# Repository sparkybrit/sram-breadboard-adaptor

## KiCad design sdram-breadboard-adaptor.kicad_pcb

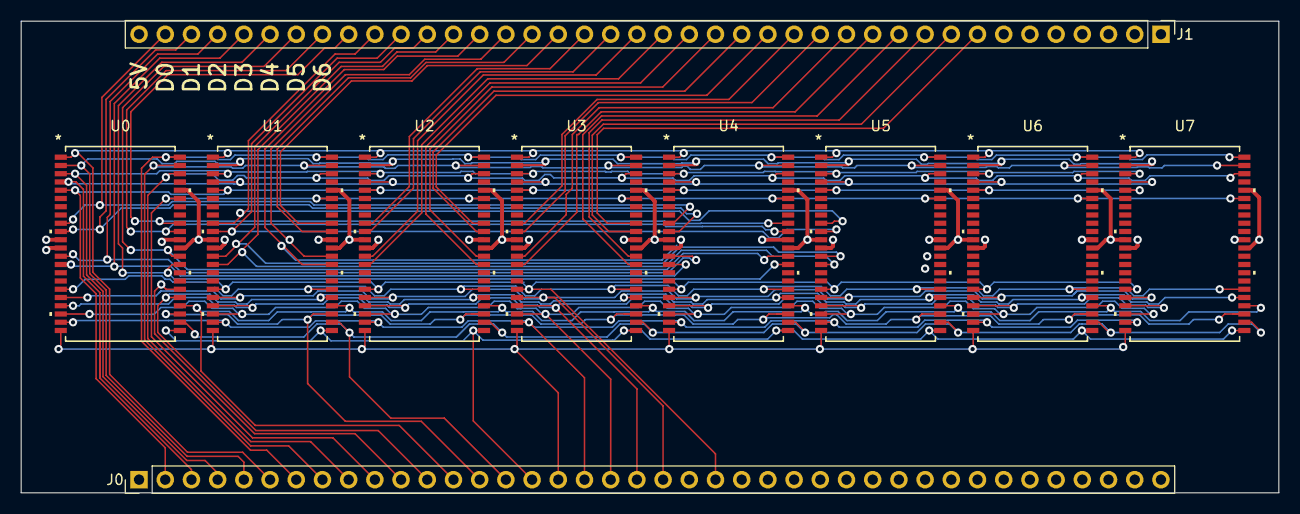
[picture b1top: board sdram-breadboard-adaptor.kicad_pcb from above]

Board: 4 copper layers, 121.9 x 45.7 mm, 10 parts (0 on the bottom side), 63 nets.

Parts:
J0, J1: Conn_01x40; PinHeader_1x40_P2.54mm_Vertical
U0, U1, U2, U3, U4, U5, U6, U7: LY62W10248ML-55LLI; TSOP-II-44_400MIL_LTK

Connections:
+5V: J0.1, J1.40, U0.11 (VCC), U0.33 (VCC), U0.40 (CE2), U1.11 (VCC), U1.33 (VCC), U1.40 (CE2), U2.11 (VCC), U2.33 (VCC), U2.40 (CE2), U3.11 (VCC), U3.33 (VCC), U3.40 (CE2), U4.11 (VCC), U4.33 (VCC), U4.40 (CE2), U5.11 (VCC), U5.33 (VCC), U5.40 (CE2), U6.11 (VCC), U6.33 (VCC), U6.40 (CE2), U7.11 (VCC), U7.33 (VCC), U7.40 (CE2)
/A2: J0.2, U0.5 (A0), U1.5 (A0), U2.5 (A0), U3.5 (A0), U4.5 (A0), U5.5 (A0), U6.5 (A0), U7.5 (A0)
/A3: J0.3, U0.4 (A1), U1.4 (A1), U2.4 (A1), U3.4 (A1), U4.4 (A1), U5.4 (A1), U6.4 (A1), U7.4 (A1)
/A4: J0.4, U0.3 (A2), U1.3 (A2), U2.3 (A2), U3.3 (A2), U4.3 (A2), U5.3 (A2), U6.3 (A2), U7.3 (A2)
/A5: J0.5, U0.2 (A3), U1.2 (A3), U2.2 (A3), U3.2 (A3), U4.2 (A3), U5.2 (A3), U6.2 (A3), U7.2 (A3)
/A6: J0.6, U0.1 (A4), U1.1 (A4), U2.1 (A4), U3.1 (A4), U4.1 (A4), U5.1 (A4), U6.1 (A4), U7.1 (A4)
/A7: J0.7, U0.44 (A5), U1.44 (A5), U2.44 (A5), U3.44 (A5), U4.44 (A5), U5.44 (A5), U6.44 (A5), U7.44 (A5)
/A8: J0.8, U0.43 (A6), U1.43 (A6), U2.43 (A6), U3.43 (A6), U4.43 (A6), U5.43 (A6), U6.43 (A6), U7.43 (A6)
/A9: J0.9, U0.42 (A7), U1.42 (A7), U2.42 (A7), U3.42 (A7), U4.42 (A7), U5.42 (A7), U6.42 (A7), U7.42 (A7)
/A10: J0.10, U0.39 (A8), U1.39 (A8), U2.39 (A8), U3.39 (A8), U4.39 (A8), U5.39 (A8), U6.39 (A8), U7.39 (A8)
/A11: J0.11, U0.28 (A9), U1.28 (A9), U2.28 (A9), U3.28 (A9), U4.28 (A9), U5.28 (A9), U6.28 (A9), U7.28 (A9)
/A12: J0.12, U0.27 (A10), U1.27 (A10), U2.27 (A10), U3.27 (A10), U4.27 (A10), U5.27 (A10), U6.27 (A10), U7.27 (A10)
/A13: J0.13, U0.26 (A11), U1.26 (A11), U2.26 (A11), U3.26 (A11), U4.26 (A11), U5.26 (A11), U6.26 (A11), U7.26 (A11)
/A14: J0.14, U0.25 (A12), U1.25 (A12), U2.25 (A12), U3.25 (A12), U4.25 (A12), U5.25 (A12), U6.25 (A12), U7.25 (A12)
/A15: J0.15, U0.24 (A13), U1.24 (A13), U2.24 (A13), U3.24 (A13), U4.24 (A13), U5.24 (A13), U6.24 (A13), U7.24 (A13)
/A16: J0.16, U0.23 (A14), U1.23 (A14), U2.23 (A14), U3.23 (A14), U4.23 (A14), U5.23 (A14), U6.23 (A14), U7.23 (A14)
/A17: J0.17, U0.22 (A15), U1.22 (A15), U2.22 (A15), U3.22 (A15), U4.22 (A15), U5.22 (A15), U6.22 (A15), U7.22 (A15)
/A18: J0.18, U0.21 (A16), U1.21 (A16), U2.21 (A16), U3.21 (A16), U4.21 (A16), U5.21 (A16), U6.21 (A16), U7.21 (A16)
/A19: J0.19, U0.20 (A17), U1.20 (A17), U2.20 (A17), U3.20 (A17), U4.20 (A17), U5.20 (A17), U6.20 (A17), U7.20 (A17)
/A20: J0.20, U0.19 (A18), U1.19 (A18), U2.19 (A18), U3.19 (A18), U4.19 (A18), U5.19 (A18), U6.19 (A18), U7.19 (A18)
/A21: J0.21, U0.18 (A19), U1.18 (A19), U2.18 (A19), U3.18 (A19), U4.18 (A19), U5.18 (A19), U6.18 (A19), U7.18 (A19)
/D0: J1.39, U0.9 (DQ0), U4.9 (DQ0)
/D1: J1.38, U0.10 (DQ1), U4.10 (DQ1)
/D2: J1.37, U0.13 (DQ2), U4.13 (DQ2)
/D3: J1.36, U0.14 (DQ3), U4.14 (DQ3)
/D4: J1.35, U0.31 (DQ4), U4.31 (DQ4)
/D5: J1.34, U0.32 (DQ5), U4.32 (DQ5)
/D6: J1.33, U0.35 (DQ6), U4.35 (DQ6)
/D7: J1.32, U0.36 (DQ7), U4.36 (DQ7)
/D8: J1.31, U1.9 (DQ0), U5.9 (DQ0)
/D9: J1.30, U1.10 (DQ1), U5.10 (DQ1)
/D10: J1.29, U1.13 (DQ2), U5.13 (DQ2)
/D11: J1.28, U1.14 (DQ3), U5.14 (DQ3)
/D12: J1.27, U1.31 (DQ4), U5.31 (DQ4)
/D13: J1.26, U1.32 (DQ5), U5.32 (DQ5)
/D14: J1.25, U1.35 (DQ6), U5.35 (DQ6)
/D15: J1.24, U1.36 (DQ7), U5.36 (DQ7)
/D16: J1.23, U2.9 (DQ0), U6.9 (DQ0)
/D17: J1.22, U2.10 (DQ1), U6.10 (DQ1)
/D18: J1.21, U2.13 (DQ2), U6.13 (DQ2)
/D19: J1.20, U2.14 (DQ3), U6.14 (DQ3)
/D20: J1.19, U2.31 (DQ4), U6.31 (DQ4)
/D21: J1.18, U2.32 (DQ5), U6.32 (DQ5)
/D22: J1.17, U2.35 (DQ6), U6.35 (DQ6)
/D23: J1.16, U2.36 (DQ7), U6.36 (DQ7)
/D24: J1.15, U3.9 (DQ0), U7.9 (DQ0)
/D25: J1.14, U3.10 (DQ1), U7.10 (DQ1)
/D26: J1.13, U3.13 (DQ2), U7.13 (DQ2)
/D27: J1.12, U3.14 (DQ3), U7.14 (DQ3)
/D28: J1.11, U3.31 (DQ4), U7.31 (DQ4)
/D29: J1.10, U3.32 (DQ5), U7.32 (DQ5)
/D30: J1.9, U3.35 (DQ6), U7.35 (DQ6)
/D31: J1.8, U3.36 (DQ7), U7.36 (DQ7)
/R/W: J0.23, U0.17 (WE#), U1.17 (WE#), U2.17 (WE#), U3.17 (WE#), U4.17 (WE#), U5.17 (WE#), U6.17 (WE#), U7.17 (WE#)
/~CEA0: J0.24, U0.6 (CE#)
/~CEA1: J0.25, U1.6 (CE#)
/~CEA2: J0.26, U2.6 (CE#)
/~CEA3: J0.27, U3.6 (CE#)
/~CEB0: J0.28, U4.6 (CE#)
/~CEB1: J0.29, U5.6 (CE#)
/~CEB2: J0.30, U6.6 (CE#)
/~CEB3: J0.31, U7.6 (CE#)
GND: J0.22, J0.40, J1.1, U0.12 (VSS), U0.34 (VSS), U0.41 (OE#), U1.12 (VSS), U1.34 (VSS), U1.41 (OE#), U2.12 (VSS), U2.34 (VSS), U2.41 (OE#), U3.12 (VSS), U3.34 (VSS), U3.41 (OE#), U4.12 (VSS), U4.34 (VSS), U4.41 (OE#), U5.12 (VSS), U5.34 (VSS), U5.41 (OE#), U6.12 (VSS), U6.34 (VSS), U6.41 (OE#), U7.12 (VSS), U7.34 (VSS), U7.41 (OE#)

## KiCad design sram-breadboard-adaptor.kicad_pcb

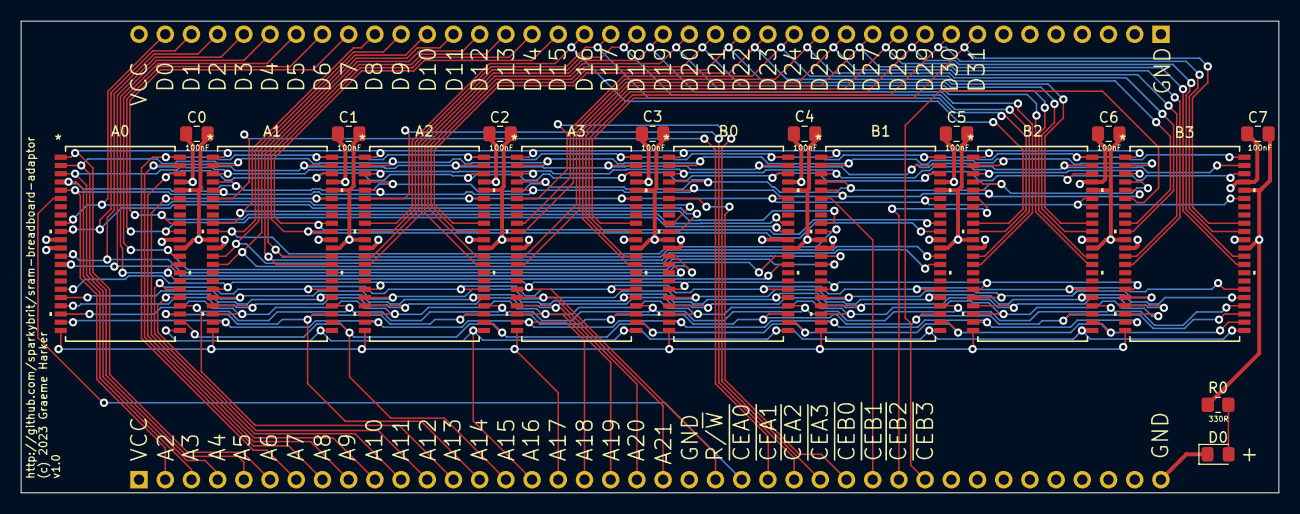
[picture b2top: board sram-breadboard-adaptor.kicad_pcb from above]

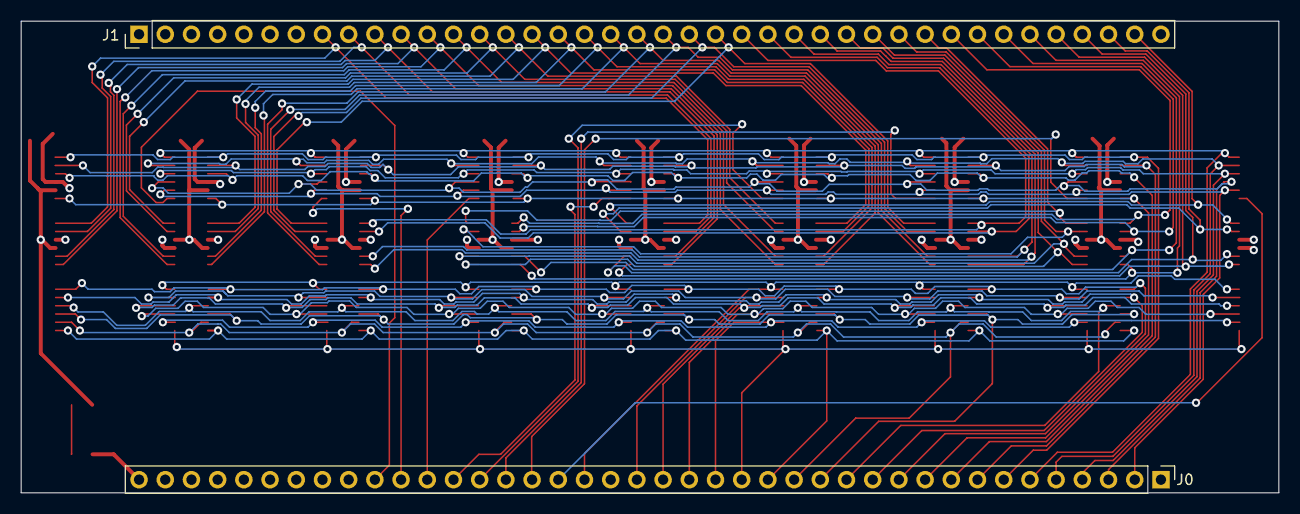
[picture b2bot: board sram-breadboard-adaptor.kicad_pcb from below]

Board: 4 copper layers, 121.9 x 45.7 mm, 20 parts (2 on the bottom side), 64 nets.

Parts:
A0, A1, A2, A3: LY62W10248ML-55LLI; TSOP-II-44_400MIL_LTK
B0, B1, B2, B3: LY62W10248ML-55LLI; TSOP-II-44_400MIL_LTK
C0, C2, C3, C4, C5, C6, C7: 100nF; C_0805_2012Metric_Pad1.18x1.45mm_HandSolder
C1: 110nF; C_0805_2012Metric_Pad1.18x1.45mm_HandSolder
D0: LED; LED_0805_2012Metric_Pad1.15x1.40mm_HandSolder
J0, J1: Conn_01x40; PinHeader_1x40_P2.54mm_Vertical
R0: 330R; R_0805_2012Metric_Pad1.20x1.40mm_HandSolder

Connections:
+5V: A0.11 (VCC), A0.33 (VCC), A0.40 (CE2), A1.11 (VCC), A1.33 (VCC), A1.40 (CE2), A2.11 (VCC), A2.33 (VCC), A2.40 (CE2), A3.11 (VCC), A3.33 (VCC), A3.40 (CE2), B0.11 (VCC), B0.33 (VCC), B0.40 (CE2), B1.11 (VCC), B1.33 (VCC), B1.40 (CE2), B2.11 (VCC), B2.33 (VCC), B2.40 (CE2), B3.11 (VCC), B3.33 (VCC), B3.40 (CE2), C0.1, C1.1, C2.1, C3.1, C4.1, C5.1, C6.1, C7.1, J0.1, J1.40, R0.1
/A2: A0.5 (A0), A1.5 (A0), A2.5 (A0), A3.5 (A0), B0.5 (A0), B1.5 (A0), B2.5 (A0), B3.5 (A0), J0.2
/A3: A0.4 (A1), A1.4 (A1), A2.4 (A1), A3.4 (A1), B0.4 (A1), B1.4 (A1), B2.4 (A1), B3.4 (A1), J0.3
/A4: A0.3 (A2), A1.3 (A2), A2.3 (A2), A3.3 (A2), B0.3 (A2), B1.3 (A2), B2.3 (A2), B3.3 (A2), J0.4
/A5: A0.2 (A3), A1.2 (A3), A2.2 (A3), A3.2 (A3), B0.2 (A3), B1.2 (A3), B2.2 (A3), B3.2 (A3), J0.5
/A6: A0.1 (A4), A1.1 (A4), A2.1 (A4), A3.1 (A4), B0.1 (A4), B1.1 (A4), B2.1 (A4), B3.1 (A4), J0.6
/A7: A0.44 (A5), A1.44 (A5), A2.44 (A5), A3.44 (A5), B0.44 (A5), B1.44 (A5), B2.44 (A5), B3.44 (A5), J0.7
/A8: A0.43 (A6), A1.43 (A6), A2.43 (A6), A3.43 (A6), B0.43 (A6), B1.43 (A6), B2.43 (A6), B3.43 (A6), J0.8
/A9: A0.42 (A7), A1.42 (A7), A2.42 (A7), A3.42 (A7), B0.42 (A7), B1.42 (A7), B2.42 (A7), B3.42 (A7), J0.9
/A10: A0.39 (A8), A1.39 (A8), A2.39 (A8), A3.39 (A8), B0.39 (A8), B1.39 (A8), B2.39 (A8), B3.39 (A8), J0.10
/A11: A0.28 (A9), A1.28 (A9), A2.28 (A9), A3.28 (A9), B0.28 (A9), B1.28 (A9), B2.28 (A9), B3.28 (A9), J0.11
/A12: A0.27 (A10), A1.27 (A10), A2.27 (A10), A3.27 (A10), B0.27 (A10), B1.27 (A10), B2.27 (A10), B3.27 (A10), J0.12
/A13: A0.26 (A11), A1.26 (A11), A2.26 (A11), A3.26 (A11), B0.26 (A11), B1.26 (A11), B2.26 (A11), B3.26 (A11), J0.13
/A14: A0.25 (A12), A1.25 (A12), A2.25 (A12), A3.25 (A12), B0.25 (A12), B1.25 (A12), B2.25 (A12), B3.25 (A12), J0.14
/A15: A0.24 (A13), A1.24 (A13), A2.24 (A13), A3.24 (A13), B0.24 (A13), B1.24 (A13), B2.24 (A13), B3.24 (A13), J0.15
/A16: A0.23 (A14), A1.23 (A14), A2.23 (A14), A3.23 (A14), B0.23 (A14), B1.23 (A14), B2.23 (A14), B3.23 (A14), J0.16
/A17: A0.22 (A15), A1.22 (A15), A2.22 (A15), A3.22 (A15), B0.22 (A15), B1.22 (A15), B2.22 (A15), B3.22 (A15), J0.17
/A18: A0.21 (A16), A1.21 (A16), A2.21 (A16), A3.21 (A16), B0.21 (A16), B1.21 (A16), B2.21 (A16), B3.21 (A16), J0.18
/A19: A0.20 (A17), A1.20 (A17), A2.20 (A17), A3.20 (A17), B0.20 (A17), B1.20 (A17), B2.20 (A17), B3.20 (A17), J0.19
/A20: A0.19 (A18), A1.19 (A18), A2.19 (A18), A3.19 (A18), B0.19 (A18), B1.19 (A18), B2.19 (A18), B3.19 (A18), J0.20
/A21: A0.18 (A19), A1.18 (A19), A2.18 (A19), A3.18 (A19), B0.18 (A19), B1.18 (A19), B2.18 (A19), B3.18 (A19), J0.21
/D0: A0.9 (DQ0), B0.9 (DQ0), J1.39
/D1: A0.10 (DQ1), B0.10 (DQ1), J1.38
/D2: A0.13 (DQ2), B0.13 (DQ2), J1.37
/D3: A0.14 (DQ3), B0.14 (DQ3), J1.36
/D4: A0.31 (DQ4), B0.31 (DQ4), J1.35
/D5: A0.32 (DQ5), B0.32 (DQ5), J1.34
/D6: A0.35 (DQ6), B0.35 (DQ6), J1.33
/D7: A0.36 (DQ7), B0.36 (DQ7), J1.32
/D8: A1.9 (DQ0), B1.9 (DQ0), J1.31
/D9: A1.10 (DQ1), B1.10 (DQ1), J1.30
/D10: A1.13 (DQ2), B1.13 (DQ2), J1.29
/D11: A1.14 (DQ3), B1.14 (DQ3), J1.28
/D12: A1.31 (DQ4), B1.31 (DQ4), J1.27
/D13: A1.32 (DQ5), B1.32 (DQ5), J1.26
/D14: A1.35 (DQ6), B1.35 (DQ6), J1.25
/D15: A1.36 (DQ7), B1.36 (DQ7), J1.24
/D16: A2.9 (DQ0), B2.9 (DQ0), J1.23
/D17: A2.10 (DQ1), B2.10 (DQ1), J1.22
/D18: A2.13 (DQ2), B2.13 (DQ2), J1.21
/D19: A2.14 (DQ3), B2.14 (DQ3), J1.20
/D20: A2.31 (DQ4), B2.31 (DQ4), J1.19
/D21: A2.32 (DQ5), B2.32 (DQ5), J1.18
/D22: A2.35 (DQ6), B2.35 (DQ6), J1.17
/D23: A2.36 (DQ7), B2.36 (DQ7), J1.16
/D24: A3.9 (DQ0), B3.9 (DQ0), J1.15
/D25: A3.10 (DQ1), B3.10 (DQ1), J1.14
/D26: A3.13 (DQ2), B3.13 (DQ2), J1.13
/D27: A3.14 (DQ3), B3.14 (DQ3), J1.12
/D28: A3.31 (DQ4), B3.31 (DQ4), J1.11
/D29: A3.32 (DQ5), B3.32 (DQ5), J1.10
/D30: A3.35 (DQ6), B3.35 (DQ6), J1.9
/D31: A3.36 (DQ7), B3.36 (DQ7), J1.8
/R/W: A0.17 (WE#), A1.17 (WE#), A2.17 (WE#), A3.17 (WE#), B0.17 (WE#), B1.17 (WE#), B2.17 (WE#), B3.17 (WE#), J0.23
/~CEA0: A0.6 (CE#), J0.24
/~CEA1: A1.6 (CE#), J0.25
/~CEA2: A2.6 (CE#), J0.26
/~CEA3: A3.6 (CE#), J0.27
/~CEB0: B0.6 (CE#), J0.28
/~CEB1: B1.6 (CE#), J0.29
/~CEB2: B2.6 (CE#), J0.30
/~CEB3: B3.6 (CE#), J0.31
GND: A0.12 (VSS), A0.34 (VSS), A0.41 (OE#), A1.12 (VSS), A1.34 (VSS), A1.41 (OE#), A2.12 (VSS), A2.34 (VSS), A2.41 (OE#), A3.12 (VSS), A3.34 (VSS), A3.41 (OE#), B0.12 (VSS), B0.34 (VSS), B0.41 (OE#), B1.12 (VSS), B1.34 (VSS), B1.41 (OE#), B2.12 (VSS), B2.34 (VSS), B2.41 (OE#), B3.12 (VSS), B3.34 (VSS), B3.41 (OE#), C0.2, C1.2, C2.2, C3.2, C4.2, C5.2, C6.2, C7.2, D0.1 (K), J0.22, J0.40, J1.1
unnamed: D0.2 (A), R0.2

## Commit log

2023-06-02 Add *-backups to .gitignore
2023-06-02 Add power flags
2023-06-02 Add pcb layout
2023-06-03 add 4 more chips
2023-06-03 add silkscreen
2023-06-04 add data bus connections
2023-06-04 add bypass caps
2023-06-05 rename project from sdram- to sram-
2023-06-05 add *.kicad_prl and fp-info-cache to .gitignore
2023-06-05 v1.0 candidate
2023-06-05 First production run
2023-06-05 add gerbers folder to .gitignore
2023-06-05 add .gitignore KiCad template

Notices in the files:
sram-breadboard-adaptor.kicad_pcb:
(c) 2023 Graeme Harker
